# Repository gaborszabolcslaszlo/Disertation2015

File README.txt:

Dolgozat/Allamvizsgadolgozat/utolsoverzio/GaborSzabolcsLaszlo_v10tanar .pdf

Hasznalt Programok:
-Matlab verzo: Matlab2014a -GUI
	      Matlab2013b -SystemGenerator

-Xilinx edk,sdk 14.7
-Autodsek Inventor 2015
-Altium Designer 14
-yEdGraph editor es Visio 2013
-Microsoft visio
-GeoGebra rajzok a modelhez

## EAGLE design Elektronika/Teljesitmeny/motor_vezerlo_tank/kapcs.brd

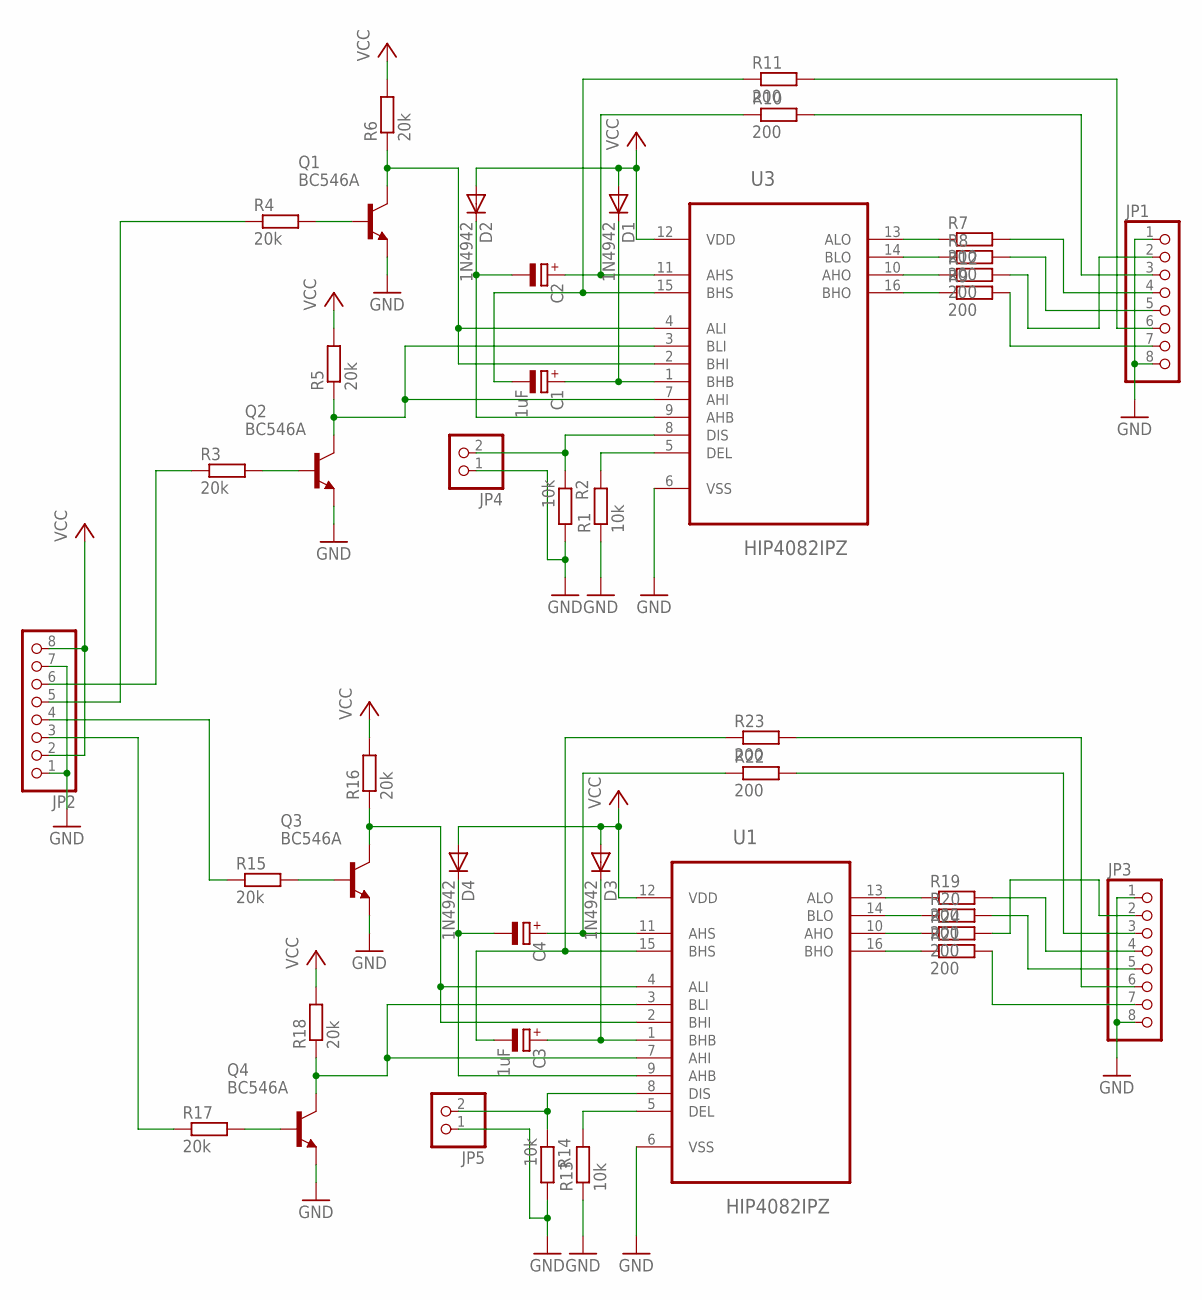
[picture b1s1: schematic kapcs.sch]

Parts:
C1, C3: 1uF; E2,5-5
C2, C4: CPOL-EUE2.5-5; E2,5-5
D1, D2, D3, D4: 1N4942; DO41-10
JP1, JP2, JP3: PINHD-1X8; 1X08
JP4, JP5: PINHD-1X2; 1X02
Q1, Q2, Q3, Q4: BC546A; TO92-EBC
R1, R2, R13, R14: 10k; 0207/7
R3, R4, R5, R6, R15, R16, R17, R18: 20k; 0207/7
R7, R8, R9, R10, R11, R12, R19, R20, R21, R22, R23, R24: 200; 0207/7
U1, U3: HIP4082IPZ; DIP254P762X533-16

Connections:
GND: JP1.1, JP1.8, JP2.1, JP2.7, JP3.1, JP3.8, JP4.1, JP5.1, Q1.E, Q2.E, Q3.E, Q4.E, R1.1, R2.2, R13.1, R14.2, U1.6 (VSS), U3.6 (VSS)
unnamed: C1.+, D1.C, U3.1 (BHB)
unnamed: R1.2, U3.5 (DEL)
unnamed: C2.+, R10.1, U3.11 (AHS)
unnamed: C2.-, D2.C, U3.9 (AHB)
unnamed: C1.-, R11.1, U3.15 (BHS)
unnamed: JP4.2, R2.1, U3.8 (DIS)
unnamed: Q1.B, R4.2
unnamed: R9.1, U3.16 (BHO)
unnamed: Q2.C, R5.1, U3.3 (BLI), U3.7 (AHI)
unnamed: Q2.B, R3.2
unnamed: Q1.C, R6.1, U3.2 (BHI), U3.4 (ALI)
unnamed: R12.1, U3.10 (AHO)
unnamed: R8.1, U3.14 (BLO)
unnamed: R7.1, U3.13 (ALO)
unnamed: JP1.3, R10.2
unnamed: JP1.4, R7.2
unnamed: JP1.5, R8.2
unnamed: JP1.2, R12.2
unnamed: JP1.7, R9.2
unnamed: Q3.B, R15.2
unnamed: Q4.C, R18.1, U1.3 (BLI), U1.7 (AHI)
unnamed: Q4.B, R17.2
unnamed: Q3.C, R16.1, U1.2 (BHI), U1.4 (ALI)
unnamed: JP2.4, R15.1
unnamed: C3.+, D3.C, U1.1 (BHB)
unnamed: C3.-, R23.1, U1.15 (BHS)
unnamed: C4.+, R22.1, U1.11 (AHS)
unnamed: C4.-, D4.C, U1.9 (AHB)
unnamed: R13.2, U1.5 (DEL)
unnamed: JP5.2, R14.1, U1.8 (DIS)
unnamed: R21.1, U1.16 (BHO)
unnamed: R24.1, U1.10 (AHO)
unnamed: R20.1, U1.14 (BLO)
unnamed: R19.1, U1.13 (ALO)
unnamed: JP3.6, R23.2
unnamed: JP3.3, R22.2
unnamed: JP3.4, R19.2
unnamed: JP3.5, R20.2
unnamed: JP3.2, R24.2
unnamed: JP2.5, R4.1
unnamed: JP2.6, R3.1
unnamed: JP3.7, R21.2
unnamed: JP2.3, R17.1
unnamed: JP1.6, R11.2
VCC: D1.A, D2.A, D3.A, D4.A, JP2.2, JP2.8, R5.2, R6.2, R16.2, R18.2, U1.12 (VDD), U3.12 (VDD)

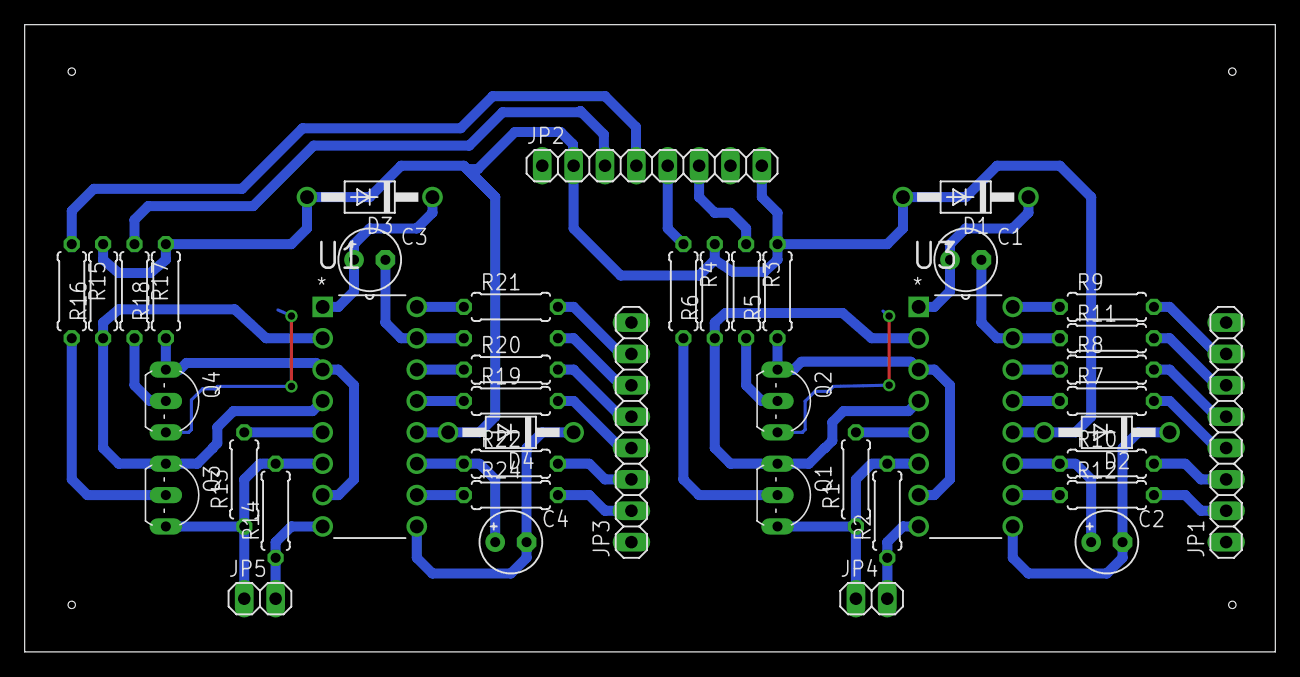
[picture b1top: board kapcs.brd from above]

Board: 2 copper layers, 101.3 x 50.8 mm, 43 parts (1 on the bottom side), 46 nets.

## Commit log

2025-05-11 Dissertation_Thesis 2015_4Leg_4CaterpilarRobot
